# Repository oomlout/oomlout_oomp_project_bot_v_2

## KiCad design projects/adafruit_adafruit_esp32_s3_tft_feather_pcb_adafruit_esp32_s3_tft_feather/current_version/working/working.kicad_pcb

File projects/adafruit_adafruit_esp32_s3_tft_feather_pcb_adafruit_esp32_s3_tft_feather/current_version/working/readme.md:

# adafruit_esp32_s3_tft_feather_pcb
 
## summary 
* id: adafruit_adafruit_esp32_s3_tft_feather_pcb_adafruit_esp32_s3_tft_feather
* user: adafruit
* name: adafruit_esp32_s3_tft_feather_pcb
* board: adafruit_esp32_s3_tft_feather
* repo: https://github.com/adafruit/Adafruit-ESP32-S3-TFT-Feather-PCB

* src_file_repo_sch: 
* src_file_repo_sch_link: https://github.com/adafruit/Adafruit-ESP32-S3-TFT-Feather-PCB/tree/main/
* full details link: https://github.com/oomlout/oomlout_oomp_project_bot_v_2/tree/main/projects/adafruit_adafruit_esp32_s3_tft_feather_pcb_adafruit_esp32_s3_tft_feather/current_version/working  

## schematic  
  
[schematic (pdf)](working_schematic.pdf) 

## pcb  

[board (pdf)](working.pdf)  

## working_bom
| Id | Designator | Footprint | Quantity | Designation | Supplier and ref |  | None | 
| --- | --- | --- | --- | --- | --- | --- | --- | 
| 1 | U3 | SOT23-5 | 1 | MCP73831T-2ACI/OT |  |  | [''] | 
| 2 | U2,U5 | SOT23-5 | 2 | AP2112-3.3 |  |  | [''] | 
| 3 | C2,C12,C7,C1,C9 | 0805-NO | 5 | 10uF |  |  | [''] | 
| 4 | C11,C5,C4,C10 | 0603-NO | 4 | 1uF |  |  | [''] | 
| 5 | R17 | 0603-NO | 1 | 1Meg |  |  | [''] | 
| 6 | U4 | BME280 | 1 | BME280 |  |  | [''] | 
| 7 | R4,R10,R2,R5,R1,R8 | 0603-NO | 6 | 5.1K |  |  | [''] | 
| 8 | U$7 | PCBFEAT-REV-040 | 1 |  |  |  | [''] | 
| 9 | R3 | RESPACK_4X0603 | 1 | 10K |  |  | [''] | 
| 10 | IC1 | WLCSP9 | 1 | LC709203F/MH |  |  | [''] | 
| 11 | R12,R7 | 0603-NO | 2 | 100K |  |  | [''] | 
| 12 | Q3 | SOT23-R | 1 | DMG3415U |  |  | [''] | 
| 13 | U$56,U$55,U$35,U$34 | FIDUCIAL_1MM | 4 | FIDUCIAL_1MM |  |  | [''] | 
| 14 | IC2 | BME680 | 1 | BME680 |  |  | [''] | 
| 15 | TP1 | TESTPOINT_ROUND_1.5MM_NO | 1 |  |  |  | [''] | 
| 16 | Q1 | SOT23-R | 1 | BSS138 |  |  | [''] | 
| 17 | D4 | SOD-123 | 1 | MBR540 |  |  | [''] | 
| 18 | @HOLE1,@HOLE0 |  | 2 |  |  |  | [''] | 
| 19 | C3,C6,C8 | 0805-NO | 3 | 10ÂµF |  |  | [''] | 
| 20 | R11 | 0603-NO | 1 | 22 |  |  | [''] | 
| 21 | U6 | QFN60_ESP32-S2-MINI-1_EXP | 1 | ESP32-S3-MINI-1 |  |  | [''] | 
| 22 | U$54,U$9 | ADAFRUIT_3.5MM | 2 |  |  |  | [''] | 
| 23 | JP3 | 1X12_ROUND_MIN | 1 |  |  |  | [''] | 
| 24 | D3 | CHIPLED_0603_NOOUTLINE | 1 | RED |  |  | [''] | 
| 25 | CHG0 | CHIPLED_0603_NOOUTLINE | 1 | ORANGE |  |  | [''] | 
| 26 | X1 | JSTPH2_BATT | 1 | JSTPH |  |  | [''] | 
| 27 | DISP1 | TFT_1.14IN_240X135_WRAPUNDER | 1 | DISP_LCD_GENERIC_SPI_1.14IN_240X135_WRAPUNDER |  |  | [''] | 
| 28 | X3 | USB_C_CUSB31-CFM2AX-01-X | 1 | USB C |  |  | [''] | 
| 29 | SW2,SW1 | BTN_KMR2_4.6X2.8 | 2 | KMR2 |  |  | [''] | 
| 30 | U$32,U$31 | MOUNTINGHOLE_2.5_PLATED | 2 | MOUNTINGHOLE2.5 |  |  | [''] | 
| 31 | LED1 | SK6805_1515 | 1 | WS2812B_SK6805_1515 |  |  | [''] | 
| 32 | JP1 | 1X16_ROUND_MIN | 1 |  |  |  | [''] | 
| 33 | CONN1 | JST_SH4_RA | 1 | STEMMA_I2C_QTRA |  |  | [''] | 

## bom_schematic
| Ref | Qnty | Value | Cmp name | Footprint | Description | Vendor | DNP | 
| --- | --- | --- | --- | --- | --- | --- | --- | 
| C1, C2, C7, C9, C12 | 5 | 10uF | CAP_CERAMIC0805-NOOUTLINE | working:0805-NO |  |  |  | 
| C3, C6, C8 | 3 | 10ÂµF | CAP_CERAMIC0805-NOOUTLINE | working:0805-NO |  |  |  | 
| C4, C5, C10, C11 | 4 | 1uF | CAP_CERAMIC0603_NO | working:0603-NO |  |  |  | 
| CHG0 | 1 | ORANGE | LED0603_NOOUTLINE | working:CHIPLED_0603_NOOUTLINE |  |  |  | 
| CONN1 | 1 | STEMMA_I2C_QTRA | STEMMA_I2C_QTRA | working:JST_SH4_RA |  |  |  | 
| D3 | 1 | RED | LED0603_NOOUTLINE | working:CHIPLED_0603_NOOUTLINE |  |  |  | 
| D4 | 1 | MBR540 | DIODE-SCHOTTKYSOD-123 | working:SOD-123 |  |  |  | 
| DISP1 | 1 | DISP_LCD_GENERIC_SPI_1.14IN_240X135_WRAPUNDER | DISP_LCD_GENERIC_SPI_1.14IN_240X135_WRAPUNDER | working:TFT_1.14IN_240X135_WRAPUNDER |  |  |  | 
| IC1 | 1 | LC709203F/MH | LC709203F/MH | working:WLCSP9 |  |  |  | 
| IC2 | 1 | BME680 | BME680 | working:BME680 |  |  |  | 
| JP1 | 1 | HEADER-1X16_MIN | HEADER-1X16_MIN | working:1X16_ROUND_MIN |  |  |  | 
| JP3 | 1 | HEADER-1X12_MIN | HEADER-1X12_MIN | working:1X12_ROUND_MIN |  |  |  | 
| LED1 | 1 | WS2812B_SK6805_1515 | WS2812B_SK6805_1515 | working:SK6805_1515 |  |  |  | 
| Q1 | 1 | BSS138 | MOSFET-NREFLOW | working:SOT23-R |  |  |  | 
| Q3 | 1 | DMG3415U | MOSFET-P | working:SOT23-R |  |  |  | 
| R1, R2, R4, R5, R8, R10 | 6 | 5.1K | RESISTOR_0603_NOOUT | working:0603-NO |  |  |  | 
| R3 | 1 | 10K | RESISTOR_4PACK | working:RESPACK_4X0603 |  |  |  | 
| R7, R12 | 2 | 100K | RESISTOR_0603_NOOUT | working:0603-NO |  |  |  | 
| R11 | 1 | 22 | RESISTOR_0603_NOOUT | working:0603-NO |  |  |  | 
| R17 | 1 | 1Meg | RESISTOR_0603_NOOUT | working:0603-NO |  |  |  | 
| SW1, SW2 | 2 | KMR2 | SWITCH_TACT_SMT4.6X2.8 | working:BTN_KMR2_4.6X2.8 |  |  |  | 
| TP1 | 1 | TESTPOINTROUND1.5MMNO | TESTPOINTROUND1.5MMNO | working:TESTPOINT_ROUND_1.5MM_NO |  |  |  | 
| U2, U5 | 2 | AP2112-3.3 | VREG_SOT23-5 | working:SOT23-5 |  |  |  | 
| U3 | 1 | MCP73831T-2ACI/OT | MCP73831/2 | working:SOT23-5 |  |  |  | 
| U4 | 1 | BME280 | BME280 | working:BME280 |  |  |  | 
| U6 | 1 | ESP32-S3-MINI-1 | ESP32-S3-MINI-1 | working:QFN60_ESP32-S2-MINI-1_EXP |  |  |  | 
| U$31, U$32 | 2 | MOUNTINGHOLE2.5 | MOUNTINGHOLE2.5 | working:MOUNTINGHOLE_2.5_PLATED |  |  |  | 
| U$34, U$35, U$55, U$56 | 4 | FIDUCIAL_1MM | FIDUCIAL_1MM | working:FIDUCIAL_1MM |  |  |  | 
| X1 | 1 | CON_JST_PH_2PIN_MT_BATT | CON_JST_PH_2PIN_MT_BATT | working:JSTPH2_BATT |  |  |  | 
| X3 | 1 | USB C | USB_C | working:USB_C_CUSB31-CFM2AX-01-X |  |  |  |

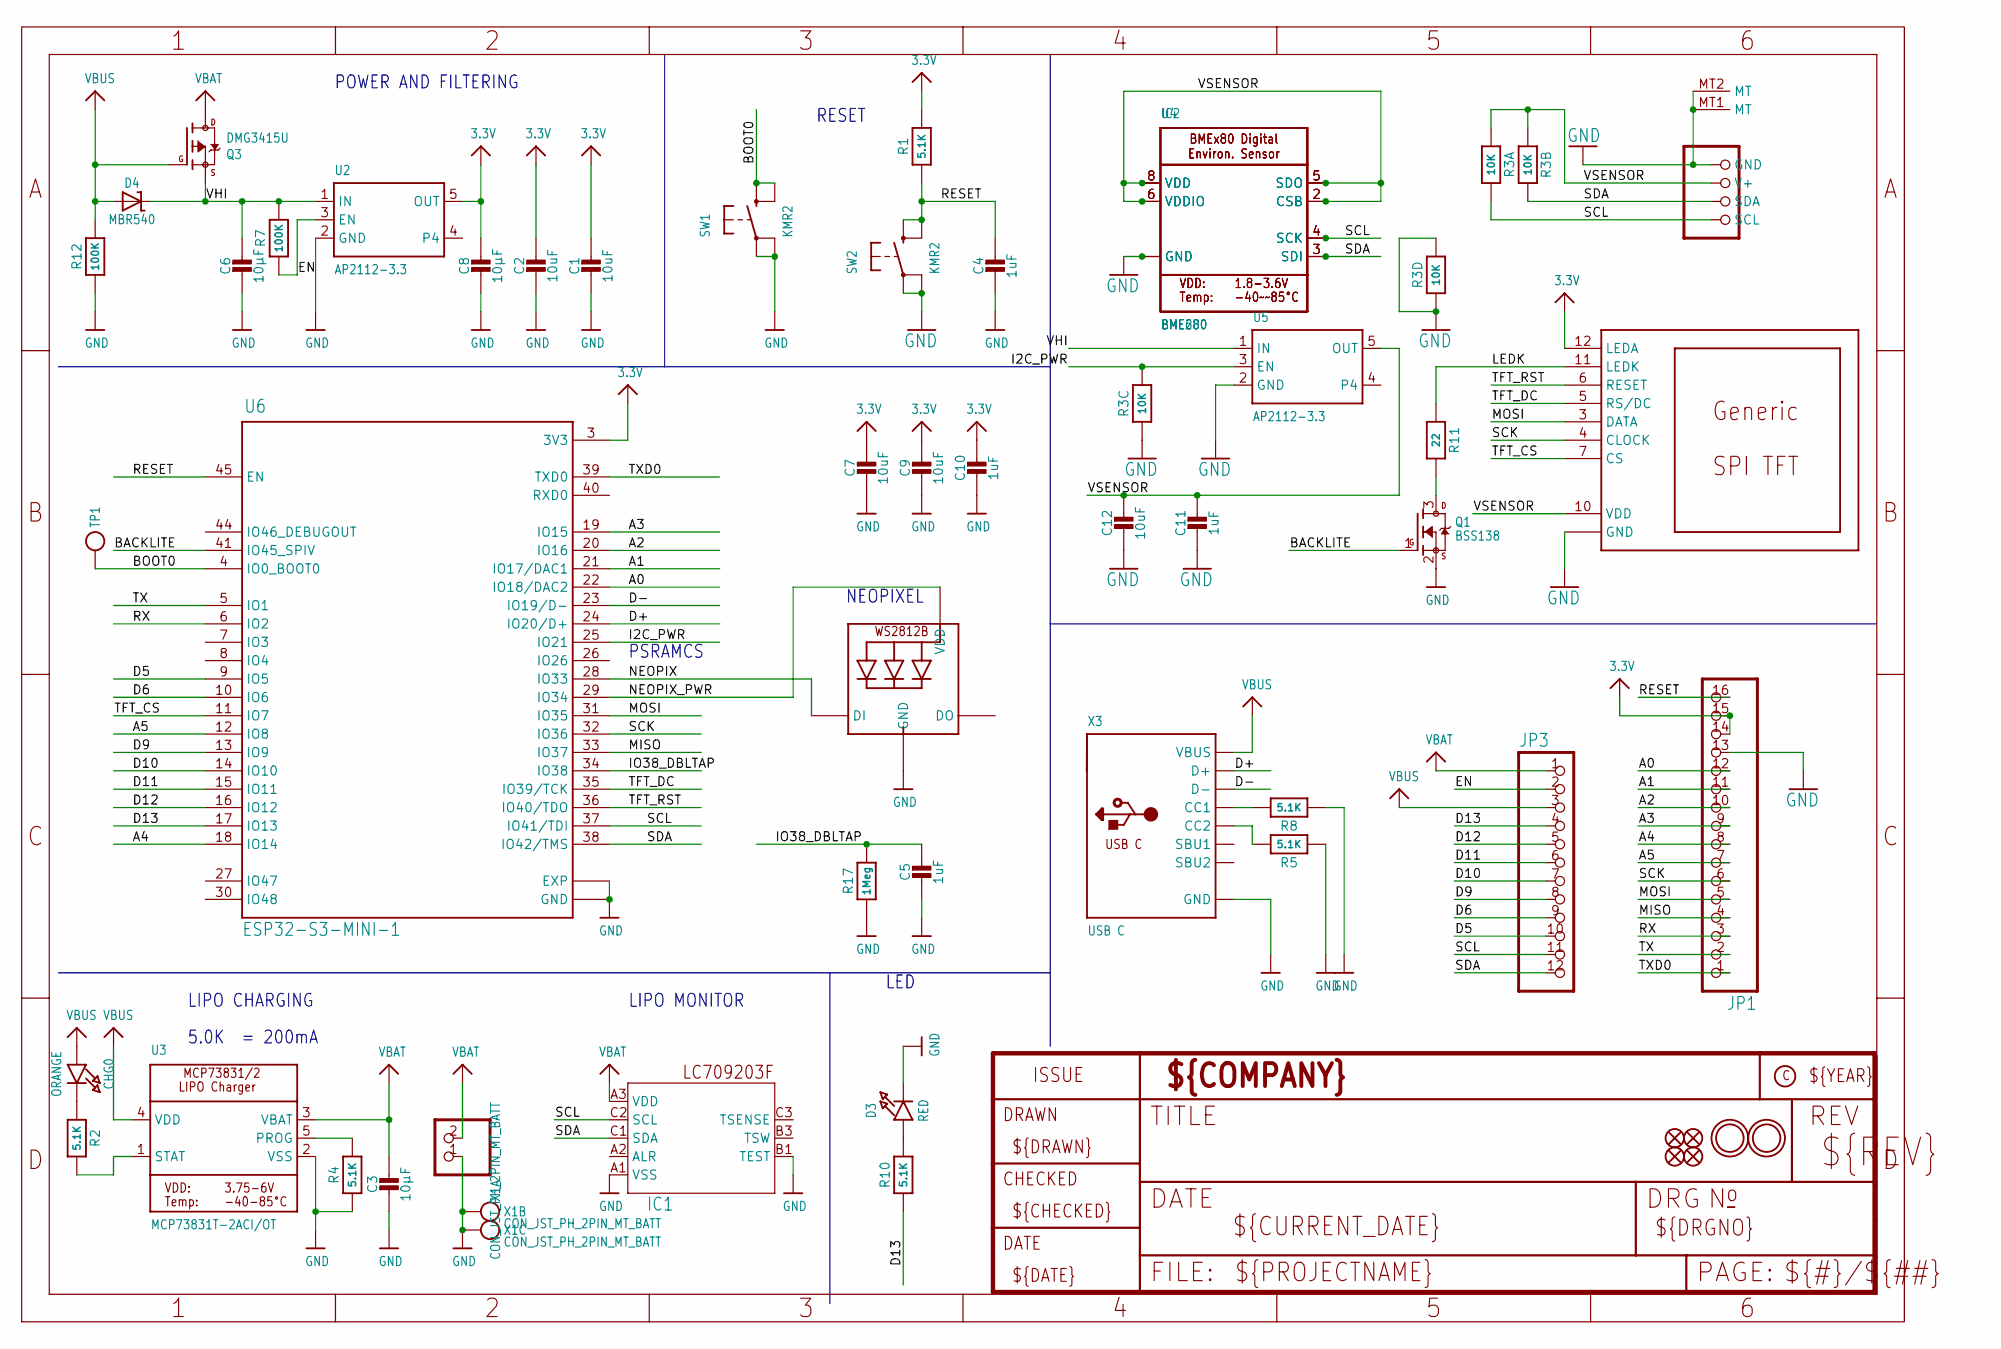
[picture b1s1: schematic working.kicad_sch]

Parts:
C1, C2, C7, C9, C12: 10uF; 0805-NO
C3, C6, C8: 10µF; 0805-NO
C4, C5, C10, C11: 1uF; 0603-NO
CHG0: ORANGE; CHIPLED_0603_NOOUTLINE
CONN1: STEMMA_I2C_QTRA; JST_SH4_RA
D3: RED; CHIPLED_0603_NOOUTLINE
D4: MBR540; SOD-123
DISP1: DISP_LCD_GENERIC_SPI_1.14IN_240X135_WRAPUNDER; TFT_1.14IN_240X135_WRAPUNDER
IC1: LC709203F/MH; WLCSP9
IC2: BME680
JP1: HEADER-1X16_MIN; 1X16_ROUND_MIN
JP3: HEADER-1X12_MIN; 1X12_ROUND_MIN
LED1: WS2812B_SK6805_1515; SK6805_1515
Q1: BSS138; SOT23-R
Q3: DMG3415U; SOT23-R
R1, R2, R4, R5, R8, R10: 5.1K; 0603-NO
R3: 10K; RESPACK_4X0603
R7, R12: 100K; 0603-NO
R11: 22; 0603-NO
R17: 1Meg; 0603-NO
SW1, SW2: KMR2; BTN_KMR2_4.6X2.8
TP1: TESTPOINTROUND1.5MMNO; TESTPOINT_ROUND_1.5MM_NO
U2, U5: AP2112-3.3; SOT23-5
U3: MCP73831T-2ACI/OT; SOT23-5
U4: BME280
U6: ESP32-S3-MINI-1; QFN60_ESP32-S2-MINI-1_EXP
U$31, U$32: MOUNTINGHOLE2.5; MOUNTINGHOLE_2.5_PLATED
U$34, U$35, U$55, U$56: FIDUCIAL_1MM
X1: CON_JST_PH_2PIN_MT_BATT; JSTPH2_BATT
X3: USB C; USB_C_CUSB31-CFM2AX-01-X

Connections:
3.3V: C1.1, C2.1, C7.1, C8.1, C9.1, C10.1, DISP1.12 (LEDA), JP1.14, JP1.15, R1.2, U2.5 (OUT), U6.3 (3V3)
A0: JP1.12, U6.22 (IO18/DAC2)
A1: JP1.11, U6.21 (IO17/DAC1)
A2: JP1.10, U6.20 (IO16)
A3: JP1.9, U6.19 (IO15)
A4: JP1.8, U6.18 (IO14)
A5: JP1.7, U6.12 (IO8)
BACKLITE: Q1.1 (G), U6.41 (IO45_SPIV)
BOOT0: SW1.B (S), SW1.B' (S1), TP1.P$1, U6.4 (IO0_BOOT0)
D5: JP3.10, U6.9 (IO5)
D6: JP3.9, U6.10 (IO6)
D9: JP3.8, U6.13 (IO9)
D10: JP3.7, U6.14 (IO10)
D11: JP3.6, U6.15 (IO11)
D12: JP3.5, U6.16 (IO12)
D13: JP3.4, R10.1, U6.17 (IO13)
D+: U6.24 (IO20/D+), X3.A6 (D+), X3.B6 (D+)
D-: U6.23 (IO19/D-), X3.A7 (D-), X3.B7 (D-)
EN: JP3.2, R7.1, U2.3 (EN)
GND: C1.2, C2.2, C3.2, C4.2, C5.2, C6.2, C7.2, C8.2, C9.2, C10.2, C11.2, C12.2, CONN1.1 (GND), CONN1.MT1 (MT), CONN1.MT2 (MT), D3.C, DISP1.8 (GND), DISP1.13 (GND), IC1.A1 (VSS), IC1.B1 (TEST), IC2.1 (GND), IC2.7 (GND), JP1.13, LED1.4 (GND), Q1.2 (S), R3.3 (1), R3.4 (1), R3.5 (2), R4.1, R5.1, R8.1, R12.1, R17.1, SW1.A, SW1.A' (P1), SW2.A, SW2.A' (P1), U2.2 (GND), U3.2 (VSS), U4.1 (GND), U4.7 (GND), U5.2 (GND), U6.1 (GND), U6.2 (GND), U6.42 (GND), U6.43 (GND), U6.46 (GND), U6.47 (GND), U6.48 (GND), U6.49 (GND), U6.50 (GND), U6.51 (GND), U6.52 (GND), U6.53 (GND), U6.54 (GND), U6.55 (GND), U6.56 (GND), U6.57 (GND), U6.58 (GND), U6.59 (GND), U6.60 (GND), U6.61 (EXP), U6.62 (GND), U6.63 (GND), U6.64 (GND), U6.65 (GND), U6.66 (EXP), U6.67 (EXP), U6.68 (EXP), U6.69 (EXP), U6.70 (EXP), U6.71 (EXP), U6.72 (EXP), U6.73 (EXP), X1.1, X1.NC1, X1.NC2, X3.A1B12 (GND), X3.B1A12 (GND)
I2C_PWR: R3.6 (2), U5.3 (EN), U6.25 (IO21)
IO38_DBLTAP: C5.1, R17.2, U6.34 (IO38)
LEDK: DISP1.11 (LEDK), R11.1
MISO: JP1.4, U6.33 (IO37)
MOSI: DISP1.3 (DATA), JP1.5, U6.31 (IO35)
unnamed: CHG0.C, R2.1
unnamed: Q1.3 (D), R11.2
unnamed: R2.2, U3.1 (STAT)
unnamed: R4.2, U3.5 (PROG)
unnamed: D3.A, R10.2
unnamed: R8.2, X3.A5 (CC1)
unnamed: R5.2, X3.B5 (CC2)
NEOPIX: LED1.1 (DI), U6.28 (IO33)
NEOPIX_PWR: LED1.2 (VDD), U6.29 (IO34)
RESET: C4.1, JP1.16, R1.1, SW2.B (S), SW2.B' (S1), U6.45 (EN)
RX: JP1.3, U6.6 (IO2)
SCK: DISP1.4 (CLOCK), JP1.6, U6.32 (IO36)
SCL: CONN1.4 (SCL), IC1.C2 (SCL), IC2.4 (SCK), JP3.11, R3.8 (2), U4.4 (SCK), U6.37 (IO41/TDI)
SDA: CONN1.3 (SDA), IC1.C1 (SDA), IC2.3 (SDI), JP3.12, R3.7 (2), U4.3 (SDI), U6.38 (IO42/TMS)
TFT_CS: DISP1.7 (CS), U6.11 (IO7)
TFT_DC: DISP1.5 (RS/DC), U6.35 (IO39/TCK)
TFT_RST: DISP1.6 (RESET), U6.36 (IO40/TDO)
TX: JP1.2, U6.5 (IO1)
TXD0: JP1.1, U6.39 (TXD0)
VBAT: C3.1, IC1.A3 (VDD), JP3.1, Q3.3 (D), U3.3 (VBAT), X1.2
VBUS: CHG0.A, D4.A, JP3.3, Q3.1 (G), R12.2, U3.4 (VDD), X3.A4B9 (VBUS), X3.B4A9 (VBUS)
VHI: C6.1, D4.C, Q3.2 (S), R7.2, U2.1 (IN), U5.1 (IN)
VSENSOR: C11.1, C12.1, CONN1.2 (V+), DISP1.10 (VDD), IC2.2 (CSB), IC2.5 (SDO), IC2.6 (VDDIO), IC2.8 (VDD), R3.1, R3.2 (1), U4.2 (CSB), U4.5 (SDO), U4.6 (VDDIO), U4.8 (VDD), U5.5 (OUT)

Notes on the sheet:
5.0K = 200mA
LED
POWER AND FILTERING
LIPO CHARGING
PSRAMCS
NEOPIXEL
RESET
LIPO MONITOR

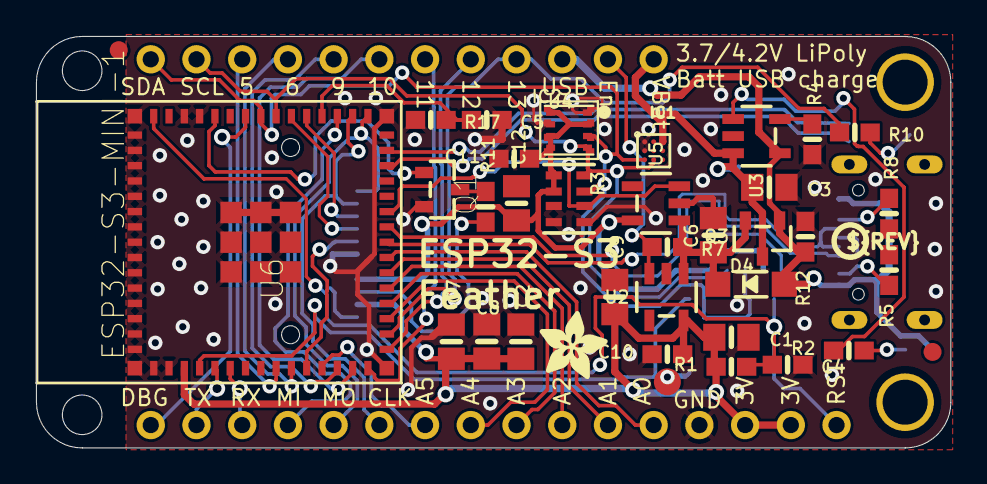
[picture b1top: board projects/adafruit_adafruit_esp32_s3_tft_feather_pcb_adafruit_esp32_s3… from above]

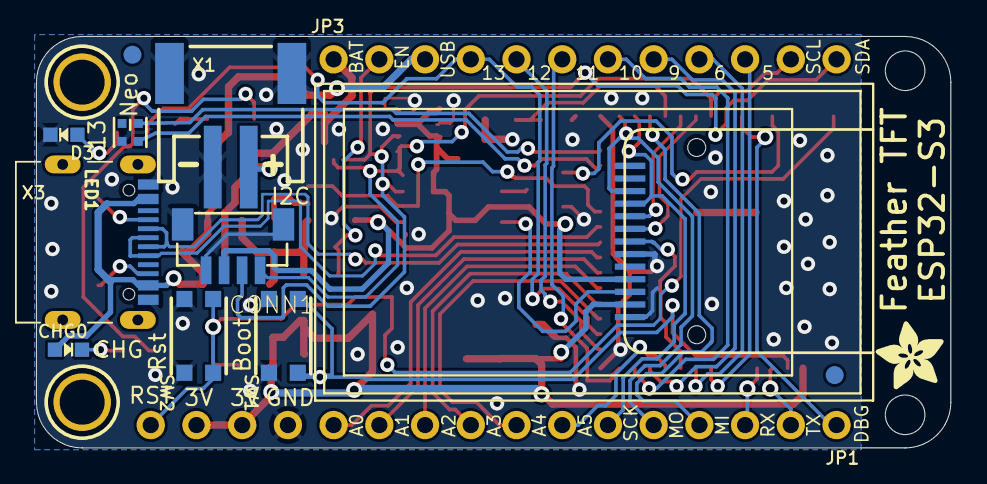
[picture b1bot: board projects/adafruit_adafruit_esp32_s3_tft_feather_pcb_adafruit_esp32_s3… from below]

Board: 2 copper layers, 50.8 x 22.9 mm, 56 parts (16 on the bottom side), 48 nets.

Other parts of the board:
@HOLE0, @HOLE1: (no value)
U$7: PCBFEAT-REV-040
U$9, U$54: ADAFRUIT_3.5MM

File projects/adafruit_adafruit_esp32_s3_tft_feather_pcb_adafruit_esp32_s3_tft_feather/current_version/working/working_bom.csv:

"Id";"Designator";"Footprint";"Quantity";"Designation";"Supplier and ref";
1;"U3";"SOT23-5";1;"MCP73831T-2ACI/OT";;;
2;"U2,U5";"SOT23-5";2;"AP2112-3.3";;;
3;"C2,C12,C7,C1,C9";"0805-NO";5;"10uF";;;
4;"C11,C5,C4,C10";"0603-NO";4;"1uF";;;
5;"R17";"0603-NO";1;"1Meg";;;
6;"U4";"BME280";1;"BME280";;;
7;"R4,R10,R2,R5,R1,R8";"0603-NO";6;"5.1K";;;
8;"U$7";"PCBFEAT-REV-040";1;"";;;
9;"R3";"RESPACK_4X0603";1;"10K";;;
10;"IC1";"WLCSP9";1;"LC709203F/MH";;;
11;"R12,R7";"0603-NO";2;"100K";;;
12;"Q3";"SOT23-R";1;"DMG3415U";;;
13;"U$56,U$55,U$35,U$34";"FIDUCIAL_1MM";4;"FIDUCIAL_1MM";;;
14;"IC2";"BME680";1;"BME680";;;
15;"TP1";"TESTPOINT_ROUND_1.5MM_NO";1;"";;;
16;"Q1";"SOT23-R";1;"BSS138";;;
17;"D4";"SOD-123";1;"MBR540";;;
18;"@HOLE1,@HOLE0";"";2;"";;;
19;"C3,C6,C8";"0805-NO";3;"10µF";;;
20;"R11";"0603-NO";1;"22";;;
21;"U6";"QFN60_ESP32-S2-MINI-1_EXP";1;"ESP32-S3-MINI-1";;;
22;"U$54,U$9";"ADAFRUIT_3.5MM";2;"";;;
23;"JP3";"1X12_ROUND_MIN";1;"";;;
24;"D3";"CHIPLED_0603_NOOUTLINE";1;"RED";;;
25;"CHG0";"CHIPLED_0603_NOOUTLINE";1;"ORANGE";;;
26;"X1";"JSTPH2_BATT";1;"JSTPH";;;
27;"DISP1";"TFT_1.14IN_240X135_WRAPUNDER";1;"DISP_LCD_GENERIC_SPI_1.14IN_240X135_WRAPUNDER";;;
28;"X3";"USB_C_CUSB31-CFM2AX-01-X";1;"USB C";;;
29;"SW2,SW1";"BTN_KMR2_4.6X2.8";2;"KMR2";;;
30;"U$32,U$31";"MOUNTINGHOLE_2.5_PLATED";2;"MOUNTINGHOLE2.5";;;
31;"LED1";"SK6805_1515";1;"WS2812B_SK6805_1515";;;
32;"JP1";"1X16_ROUND_MIN";1;"";;;
33;"CONN1";"JST_SH4_RA";1;"STEMMA_I2C_QTRA";;;

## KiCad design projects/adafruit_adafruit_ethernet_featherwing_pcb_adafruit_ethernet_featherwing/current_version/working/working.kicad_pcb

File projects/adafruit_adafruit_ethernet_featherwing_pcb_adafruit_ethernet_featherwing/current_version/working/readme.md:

# adafruit_ethernet_featherwing_pcb
 
## summary 
* id: adafruit_adafruit_ethernet_featherwing_pcb_adafruit_ethernet_featherwing
* user: adafruit
* name: adafruit_ethernet_featherwing_pcb
* board: adafruit_ethernet_featherwing
* repo: https://github.com/adafruit/Adafruit-Ethernet-FeatherWing-PCB

* src_file_repo_sch: 
* src_file_repo_sch_link: https://github.com/adafruit/Adafruit-Ethernet-FeatherWing-PCB/tree/master/
* full details link: https://github.com/oomlout/oomlout_oomp_project_bot_v_2/tree/main/projects/adafruit_adafruit_ethernet_featherwing_pcb_adafruit_ethernet_featherwing/current_version/working  

## schematic  
  
[schematic (pdf)](working_schematic.pdf) 

## pcb  

[board (pdf)](working.pdf)  

## working_bom
| Id | Designator | Footprint | Quantity | Designation | Supplier and ref |  | None | 
| --- | --- | --- | --- | --- | --- | --- | --- | 
| 1 | C14,C11,C12 | 0805-NO | 3 | 10uF |  |  | [''] | 
| 2 | FB2,FB1 | 0805-NO | 2 | ferrite |  |  | [''] | 
| 3 | C1,C2 | 0603-NO | 2 | 22pF |  |  | [''] | 
| 4 | U$1 | LQFP48 | 1 | W5500 |  |  | [''] | 
| 5 | JP1 | 1X03_ROUND_76 | 1 |  |  |  | [''] | 
| 6 | SW1 | BTN_KMR2_4.6X2.8 | 1 | KMR2 |  |  | [''] | 
| 7 | FID2,FID1,FID3 | FIDUCIAL_1MM | 3 | FIDUCIAL" |  |  | [''] | 
| 8 | R2 | 0603-NO | 1 | 1M |  |  | [''] | 
| 9 | U$45 | PCBFEAT-REV-040 | 1 |  |  |  | [''] | 
| 10 | R8,R15,R6,R7,R3,R5 | 0603-NO | 6 | 10K |  |  | [''] | 
| 11 | R12 | 0603-NO | 1 | 10 |  |  | [''] | 
| 12 | C10,C7,C15,C13,C8,C9 | 0603-NO | 6 | 0.1uF |  |  | [''] | 
| 13 | C3,C4 | 0603-NO | 2 | 6.8nF |  |  | [''] | 
| 14 | R4,R9,R11,R10 | 0603-NO | 4 | 49.9 |  |  | [''] | 
| 15 | R14,R13 | 0603-NO | 2 | 470 |  |  | [''] | 
| 16 | X1 | RJ45_PULSEJACK | 1 | RB1-125BAG1A |  |  | [''] | 
| 17 | MS1 | FEATHERWING_NODIM | 1 | FEATHERWING_NODIM |  |  | [''] | 
| 18 | U$49 | ADAFRUIT_3.5MM | 1 |  |  |  | [''] | 
| 19 | R1 | 0603-NO | 1 | 12.4K |  |  | [''] | 
| 20 | Y1 | CRYSTAL_3.2X2.5 | 1 | 25MHz |  |  | [''] | 
| 21 | JP2 | 1X13_ROUND_70 | 1 |  |  |  | [''] | 
| 22 | JP4 | 1X09_ROUND_70 | 1 |  |  |  | [''] | 
| 23 | C5,C6 | 0603-NO | 2 | 10nF |  |  | [''] | 
| 24 | IC1 | SOT23-5L | 1 | 74AHC1G125 |  |  | [''] | 
| 25 | SJ3,SJ2,SJ1 | SOLDERJUMPER_REFLOW_NOPASTE | 3 |  |  |  | [''] | 
| 26 | SJ4 | SOLDERJUMPER_CLOSEDWIRE | 1 |  |  |  | [''] | 
| 27 | U$48 | FEATHERLOGO_MED | 1 |  |  |  | [''] | 

## bom_schematic
| Ref | Qnty | Value | Cmp name | Footprint | Description | Vendor | DNP | 
| --- | --- | --- | --- | --- | --- | --- | --- | 
| C1, C2 | 2 | 22pF | CAP_CERAMIC0603_NO | working:0603-NO |  |  |  | 
| C3, C4 | 2 | 6.8nF | CAP_CERAMIC0603_NO | working:0603-NO |  |  |  | 
| C5, C6 | 2 | 10nF | CAP_CERAMIC0603_NO | working:0603-NO |  |  |  | 
| C7, C8, C9, C10, C13, C15 | 6 | 0.1uF | CAP_CERAMIC0603_NO | working:0603-NO |  |  |  | 
| C11, C12, C14 | 3 | 10uF | CAP_CERAMIC0805-NOOUTLINE | working:0805-NO |  |  |  | 
| FB1, FB2 | 2 | ferrite | FERRITE-0805NO | working:0805-NO |  |  |  | 
| FID1, FID2, FID3 | 3 | FIDUCIAL"" | FIDUCIAL{dblquote}{dblquote} | working:FIDUCIAL_1MM |  |  |  | 
| IC1 | 1 | 74AHC1G125 | 74AHC1G125 | working:SOT23-5L |  |  |  | 
| JP1 | 1 | HEADER-1X376MIL | HEADER-1X376MIL | working:1X03_ROUND_76 |  |  |  | 
| JP2 | 1 | HEADER-1X13 | HEADER-1X13 | working:1X13_ROUND_70 |  |  |  | 
| JP4 | 1 | HEADER-1X970MIL | HEADER-1X970MIL | working:1X09_ROUND_70 |  |  |  | 
| MS1 | 1 | FEATHERWING_NODIM | FEATHERWING_NODIM | working:FEATHERWING_NODIM |  |  |  | 
| R1 | 1 | 12.4K | RESISTOR_0603_NOOUT | working:0603-NO |  |  |  | 
| R2 | 1 | 1M | RESISTOR_0603_NOOUT | working:0603-NO |  |  |  | 
| R3, R5, R6, R7, R8, R15 | 6 | 10K | RESISTOR_0603_NOOUT | working:0603-NO |  |  |  | 
| R4, R9, R10, R11 | 4 | 49.9 | RESISTOR_0603_NOOUT | working:0603-NO |  |  |  | 
| R12 | 1 | 10 | RESISTOR_0603_NOOUT | working:0603-NO |  |  |  | 
| R13, R14 | 2 | 470 | RESISTOR_0603_NOOUT | working:0603-NO |  |  |  | 
| SJ1, SJ2, SJ3 | 3 | SOLDERJUMPERREFLOW_NOPASTE | SOLDERJUMPERREFLOW_NOPASTE | working:SOLDERJUMPER_REFLOW_NOPASTE |  |  |  | 
| SJ4 | 1 | SOLDERJUMPERCLOSED | SOLDERJUMPERCLOSED | working:SOLDERJUMPER_CLOSEDWIRE |  |  |  | 
| SW1 | 1 | KMR2 | SWITCH_TACT_SMT4.6X2.8 | working:BTN_KMR2_4.6X2.8 |  |  |  | 
| U$1 | 1 | W5500 | WIZNET_W5500 | working:LQFP48 |  |  |  | 
| X1 | 1 | RB1-125BAG1A | RJ45J0026D21BNL | working:RJ45_PULSEJACK |  |  |  | 
| Y1 | 1 | 25MHz | CRYSTAL3.2X2.5 | working:CRYSTAL_3.2X2.5 |  |  |  |

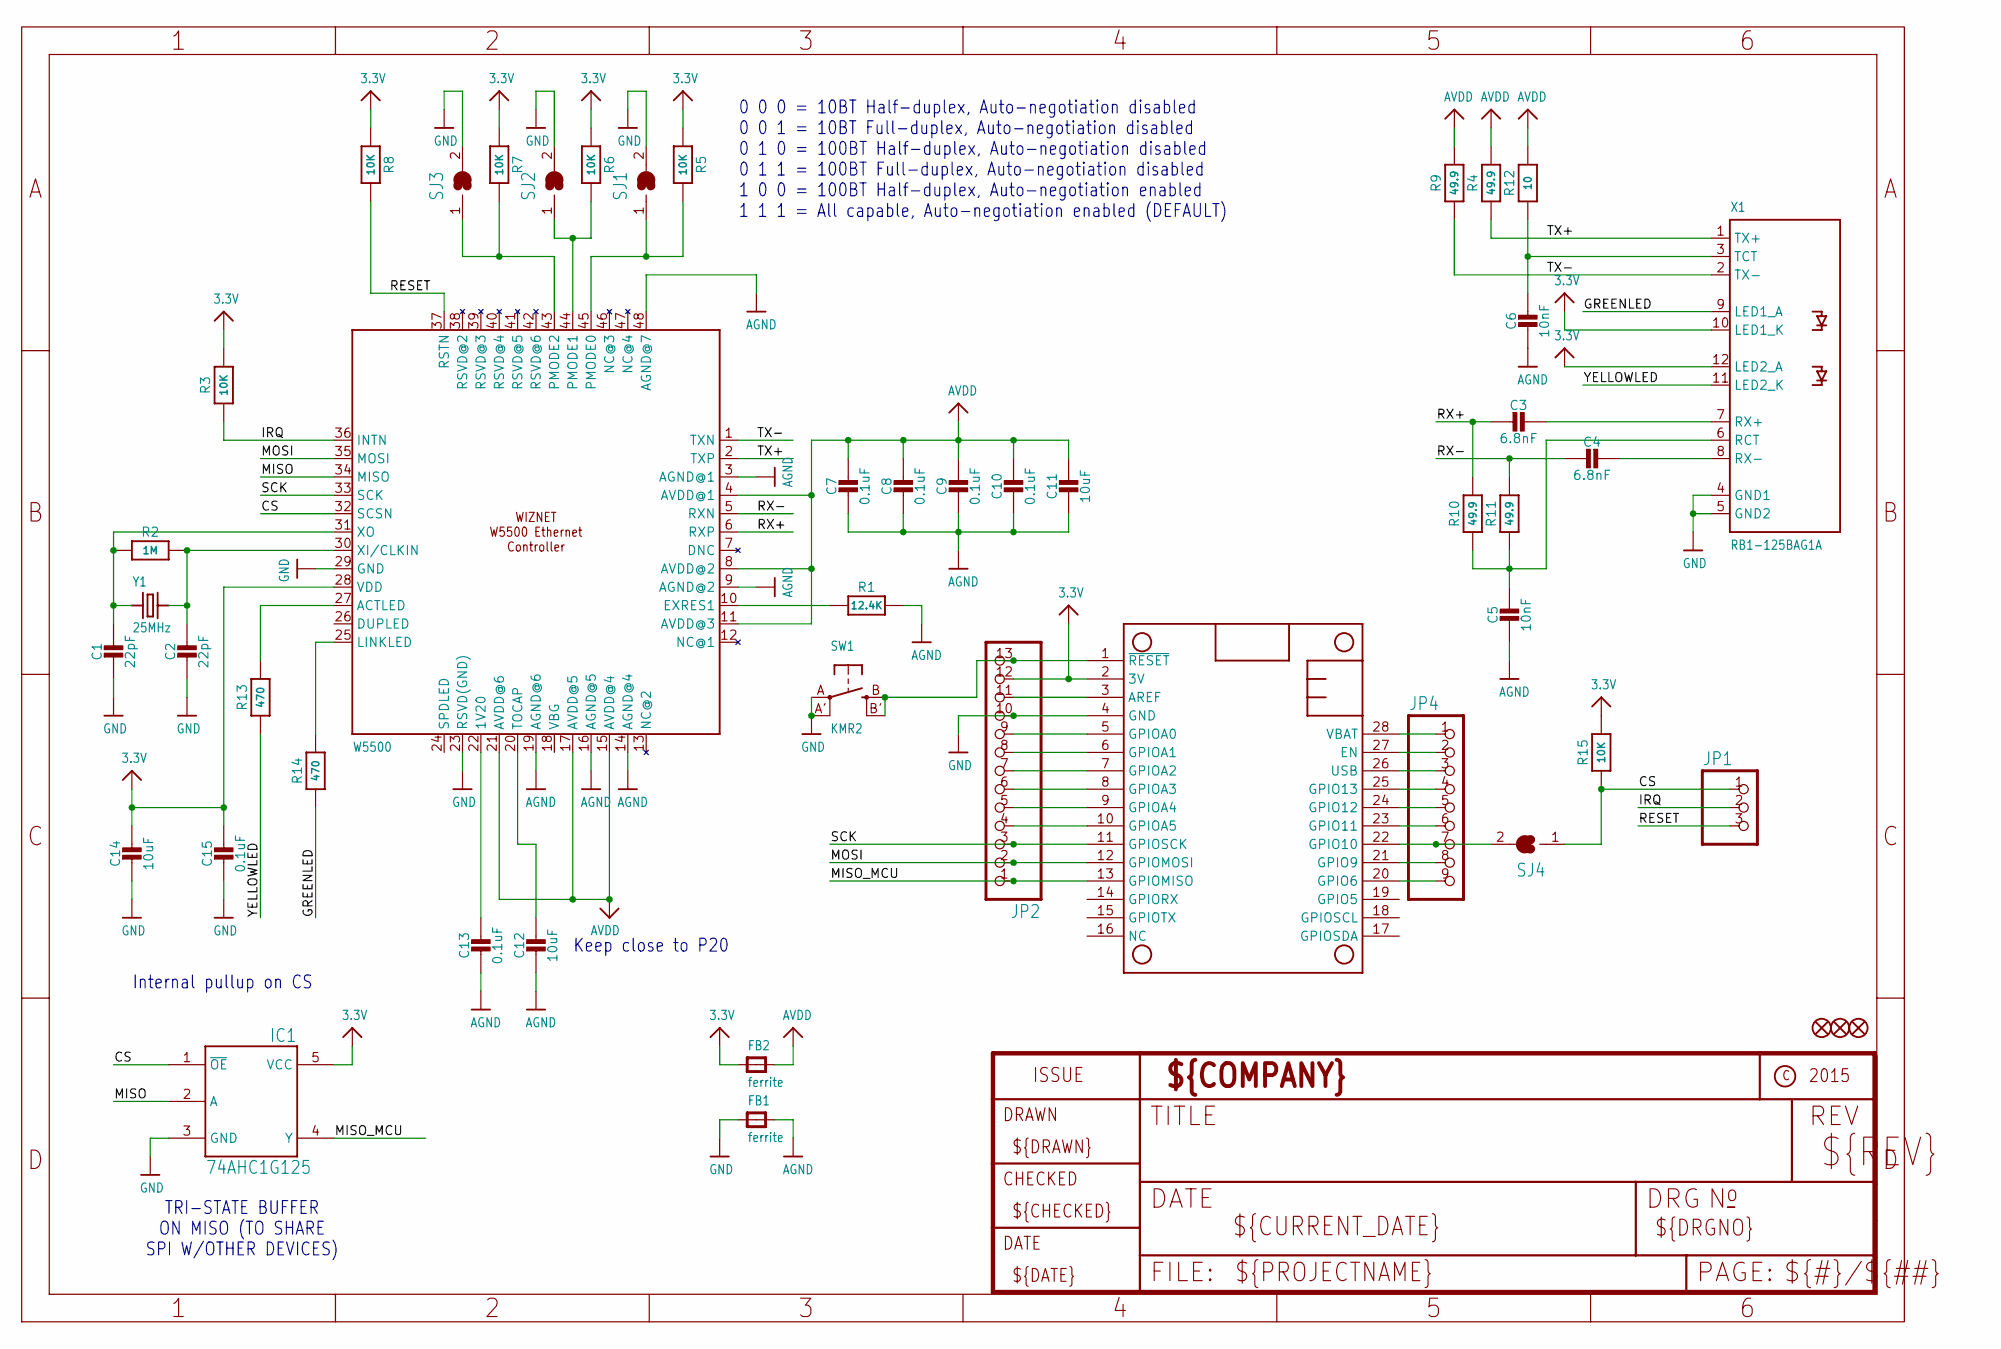
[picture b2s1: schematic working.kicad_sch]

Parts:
C1, C2: 22pF; 0603-NO
C3, C4: 6.8nF; 0603-NO
C5, C6: 10nF; 0603-NO
C7, C8, C9, C10, C13, C15: 0.1uF; 0603-NO
C11, C12, C14: 10uF; 0805-NO
FB1, FB2: ferrite; 0805-NO
FID1, FID2, FID3: FIDUCIAL""; FIDUCIAL_1MM
IC1: 74AHC1G125; SOT23-5L
JP1: HEADER-1X376MIL; 1X03_ROUND_76
JP2: HEADER-1X13; 1X13_ROUND_70
JP4: HEADER-1X970MIL; 1X09_ROUND_70
MS1: FEATHERWING_NODIM
R1: 12.4K; 0603-NO
R2: 1M; 0603-NO
R3, R5, R6, R7, R8, R15: 10K; 0603-NO
R4, R9, R10, R11: 49.9; 0603-NO
R12: 10; 0603-NO
R13, R14: 470; 0603-NO
SJ1, SJ2, SJ3: SOLDERJUMPERREFLOW_NOPASTE; SOLDERJUMPER_REFLOW_NOPASTE
SJ4: SOLDERJUMPERCLOSED; SOLDERJUMPER_CLOSEDWIRE
SW1: KMR2; BTN_KMR2_4.6X2.8
U$1: W5500; LQFP48
X1: RB1-125BAG1A; RJ45_PULSEJACK
Y1: 25MHz; CRYSTAL_3.2X2.5

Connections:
3.3V: C14.1, C15.1, FB2.1, IC1.5 (VCC), JP2.12, MS1.2 (3V), R3.2, R5.1, R6.1, R7.1, R8.1, R15.2, U$1.28 (VDD), X1.10 (LED1_K), X1.12 (LED2_A)
AGND: C5.2, C6.2, C7.2, C8.2, C9.2, C10.2, C11.2, C12.2, C13.2, FB1.2, R1.2, U$1.3 (AGND@1), U$1.9 (AGND@2), U$1.14 (AGND@4), U$1.16 (AGND@5), U$1.19 (AGND@6), U$1.48 (AGND@7)
AVDD: C7.1, C8.1, C9.1, C10.1, C11.1, FB2.2, R4.2, R9.2, R12.2, U$1.4 (AVDD@1), U$1.8 (AVDD@2), U$1.11 (AVDD@3), U$1.15 (AVDD@4), U$1.17 (AVDD@5), U$1.21 (AVDD@6)
CS: IC1.1 (~OE), JP1.1, R15.1, SJ4.1, U$1.32 (SCSN)
GND: C1.2, C2.2, C14.2, C15.2, FB1.1, IC1.3 (GND), JP2.10, MS1.4 (GND), SJ1.2, SJ2.2, SJ3.2, SW1.A, SW1.A' (P1), U$1.23 (RSVD(GND)), U$1.29 (GND), X1.4 (GND1), X1.5 (GND2)
GREENLED: R14.1, X1.9 (LED1_A)
IRQ: JP1.2, R3.1, U$1.36 (INTN)
MISO: IC1.2 (A), U$1.34 (MISO)
MISO_MCU: IC1.4 (Y), JP2.1, MS1.13 (GPIOMISO)
MOSI: JP2.2, MS1.12 (GPIOMOSI), U$1.35 (MOSI)
unnamed: C1.1, R2.1, U$1.31 (XO), Y1.1
unnamed: C2.1, R2.2, U$1.30 (XI/CLKIN), Y1.2
unnamed: R1.1, U$1.10 (EXRES1)
unnamed: R5.2, SJ1.1, U$1.45 (PMODE0)
unnamed: R6.2, SJ2.1, U$1.44 (PMODE1)
unnamed: R7.2, SJ3.1, U$1.43 (PMODE2)
unnamed: C3.1, X1.7 (RX+)
unnamed: C4.1, X1.8 (RX-)
unnamed: C5.1, R10.1, R11.1, X1.6 (RCT)
unnamed: C6.1, R12.1, X1.3 (TCT)
unnamed: C13.1, U$1.22 (1V20)
unnamed: C12.1, U$1.20 (TOCAP)
unnamed: R13.2, U$1.27 (ACTLED)
unnamed: R14.2, U$1.25 (LINKLED)
unnamed: JP4.2, MS1.27 (EN)
unnamed: JP4.4, MS1.25 (GPIO13)
unnamed: JP4.5, MS1.24 (GPIO12)
unnamed: JP4.6, MS1.23 (GPIO11)
unnamed: JP4.7, MS1.22 (GPIO10), SJ4.2
unnamed: JP4.8, MS1.21 (GPIO9)
unnamed: JP4.9, MS1.20 (GPIO6)
unnamed: JP2.13, MS1.1 (~RESET), SW1.B (S), SW1.B' (S1)
unnamed: JP2.4, MS1.10 (GPIOA5)
unnamed: JP2.5, MS1.9 (GPIOA4)
unnamed: JP2.6, MS1.8 (GPIOA3)
unnamed: JP2.7, MS1.7 (GPIOA2)
unnamed: JP2.8, MS1.6 (GPIOA1)
unnamed: JP2.9, MS1.5 (GPIOA0)
unnamed: JP2.11, MS1.3 (AREF)
RESET: JP1.3, R8.2, U$1.37 (RSTN)
RX+: C3.2, R10.2, U$1.6 (RXP)
RX-: C4.2, R11.2, U$1.5 (RXN)
SCK: JP2.3, MS1.11 (GPIOSCK), U$1.33 (SCK)
TX+: R4.1, U$1.2 (TXP), X1.1 (TX+)
TX-: R9.1, U$1.1 (TXN), X1.2 (TX-)
USB: JP4.3, MS1.26 (USB)
VBAT: JP4.1, MS1.28 (VBAT)
YELLOWLED: R13.1, X1.11 (LED2_K)

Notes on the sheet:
Keep close to P20
Internal pullup on CS
TRI-STATE BUFFER ON MISO (TO SHARE SPI W/OTHER DEVICES)
0 0 0 = 10BT Half-duplex, Auto-negotiation disabled 0 0 1 = 10BT Full-duplex, Auto-negotiation disabled 0 1 0 = 100BT Half-duplex, Auto-negotiation disabled 0 1 1 = 100BT Full-duplex, Auto-negotiation disabled 1 0 0 = 100BT Half-duplex, Auto-negotiation enabled 1 1 1 = All capable, Auto-negotiation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

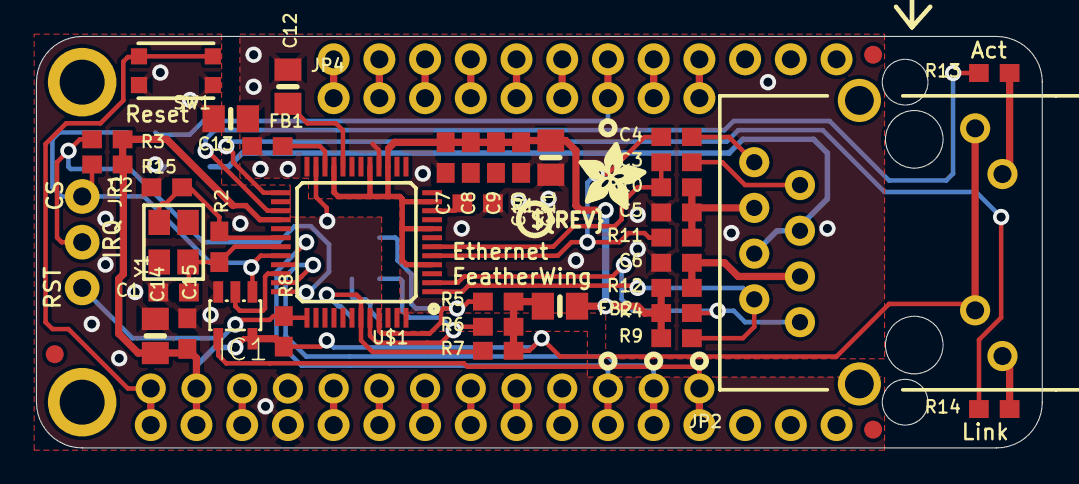
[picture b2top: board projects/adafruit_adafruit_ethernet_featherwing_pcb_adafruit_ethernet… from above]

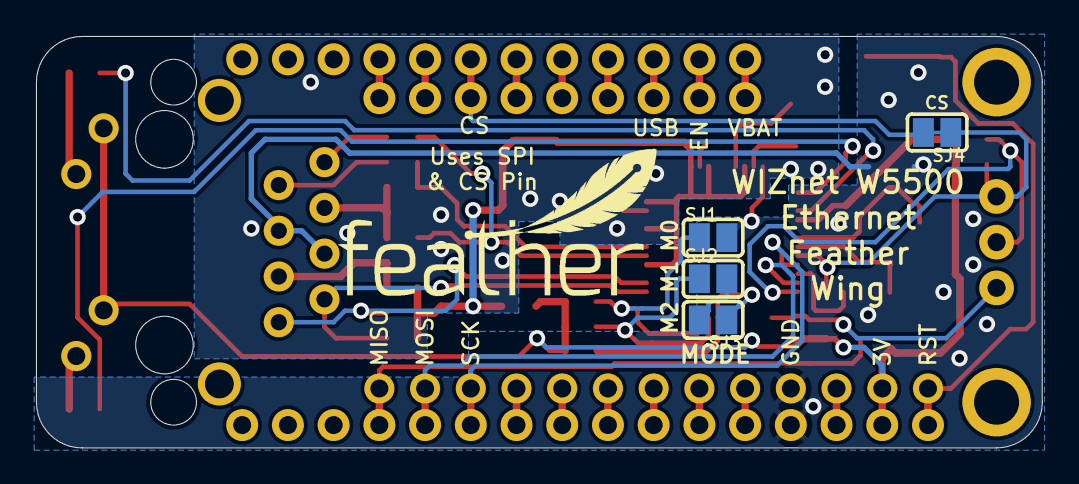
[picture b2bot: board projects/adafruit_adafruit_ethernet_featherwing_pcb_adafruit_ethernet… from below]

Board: 2 copper layers, 55.9 x 22.9 mm, 51 parts (5 on the bottom side), 48 nets.

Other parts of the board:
U$45: PCBFEAT-REV-040
U$48: FEATHERLOGO_MED
U$49: ADAFRUIT_3.5MM

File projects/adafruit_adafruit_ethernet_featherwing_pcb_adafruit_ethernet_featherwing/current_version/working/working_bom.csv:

"Id";"Designator";"Footprint";"Quantity";"Designation";"Supplier and ref";
1;"C14,C11,C12";"0805-NO";3;"10uF";;;
2;"FB2,FB1";"0805-NO";2;"ferrite";;;
3;"C1,C2";"0603-NO";2;"22pF";;;
4;"U$1";"LQFP48";1;"W5500";;;
5;"JP1";"1X03_ROUND_76";1;"";;;
6;"SW1";"BTN_KMR2_4.6X2.8";1;"KMR2";;;
7;"FID2,FID1,FID3";"FIDUCIAL_1MM";3;"FIDUCIAL""";;;
8;"R2";"0603-NO";1;"1M";;;
9;"U$45";"PCBFEAT-REV-040";1;"";;;
10;"R8,R15,R6,R7,R3,R5";"0603-NO";6;"10K";;;
11;"R12";"0603-NO";1;"10";;;
12;"C10,C7,C15,C13,C8,C9";"0603-NO";6;"0.1uF";;;
13;"C3,C4";"0603-NO";2;"6.8nF";;;
14;"R4,R9,R11,R10";"0603-NO";4;"49.9";;;
15;"R14,R13";"0603-NO";2;"470";;;
16;"X1";"RJ45_PULSEJACK";1;"RB1-125BAG1A";;;
17;"MS1";"FEATHERWING_NODIM";1;"FEATHERWING_NODIM";;;
18;"U$49";"ADAFRUIT_3.5MM";1;"";;;
19;"R1";"0603-NO";1;"12.4K";;;
20;"Y1";"CRYSTAL_3.2X2.5";1;"25MHz";;;
21;"JP2";"1X13_ROUND_70";1;"";;;
22;"JP4";"1X09_ROUND_70";1;"";;;
23;"C5,C6";"0603-NO";2;"10nF";;;
24;"IC1";"SOT23-5L";1;"74AHC1G125";;;
25;"SJ3,SJ2,SJ1";"SOLDERJUMPER_REFLOW_NOPASTE";3;"";;;
26;"SJ4";"SOLDERJUMPER_CLOSEDWIRE";1;"";;;
27;"U$48";"FEATHERLOGO_MED";1;"";;;
